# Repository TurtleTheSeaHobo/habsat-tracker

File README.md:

# HABSAT Tracker
*(awful acronym pending)*

This repository provides schematics and layouts for the hardware of a high-
altitude balloon tracker and sensor carrier of presently indeterminate name.

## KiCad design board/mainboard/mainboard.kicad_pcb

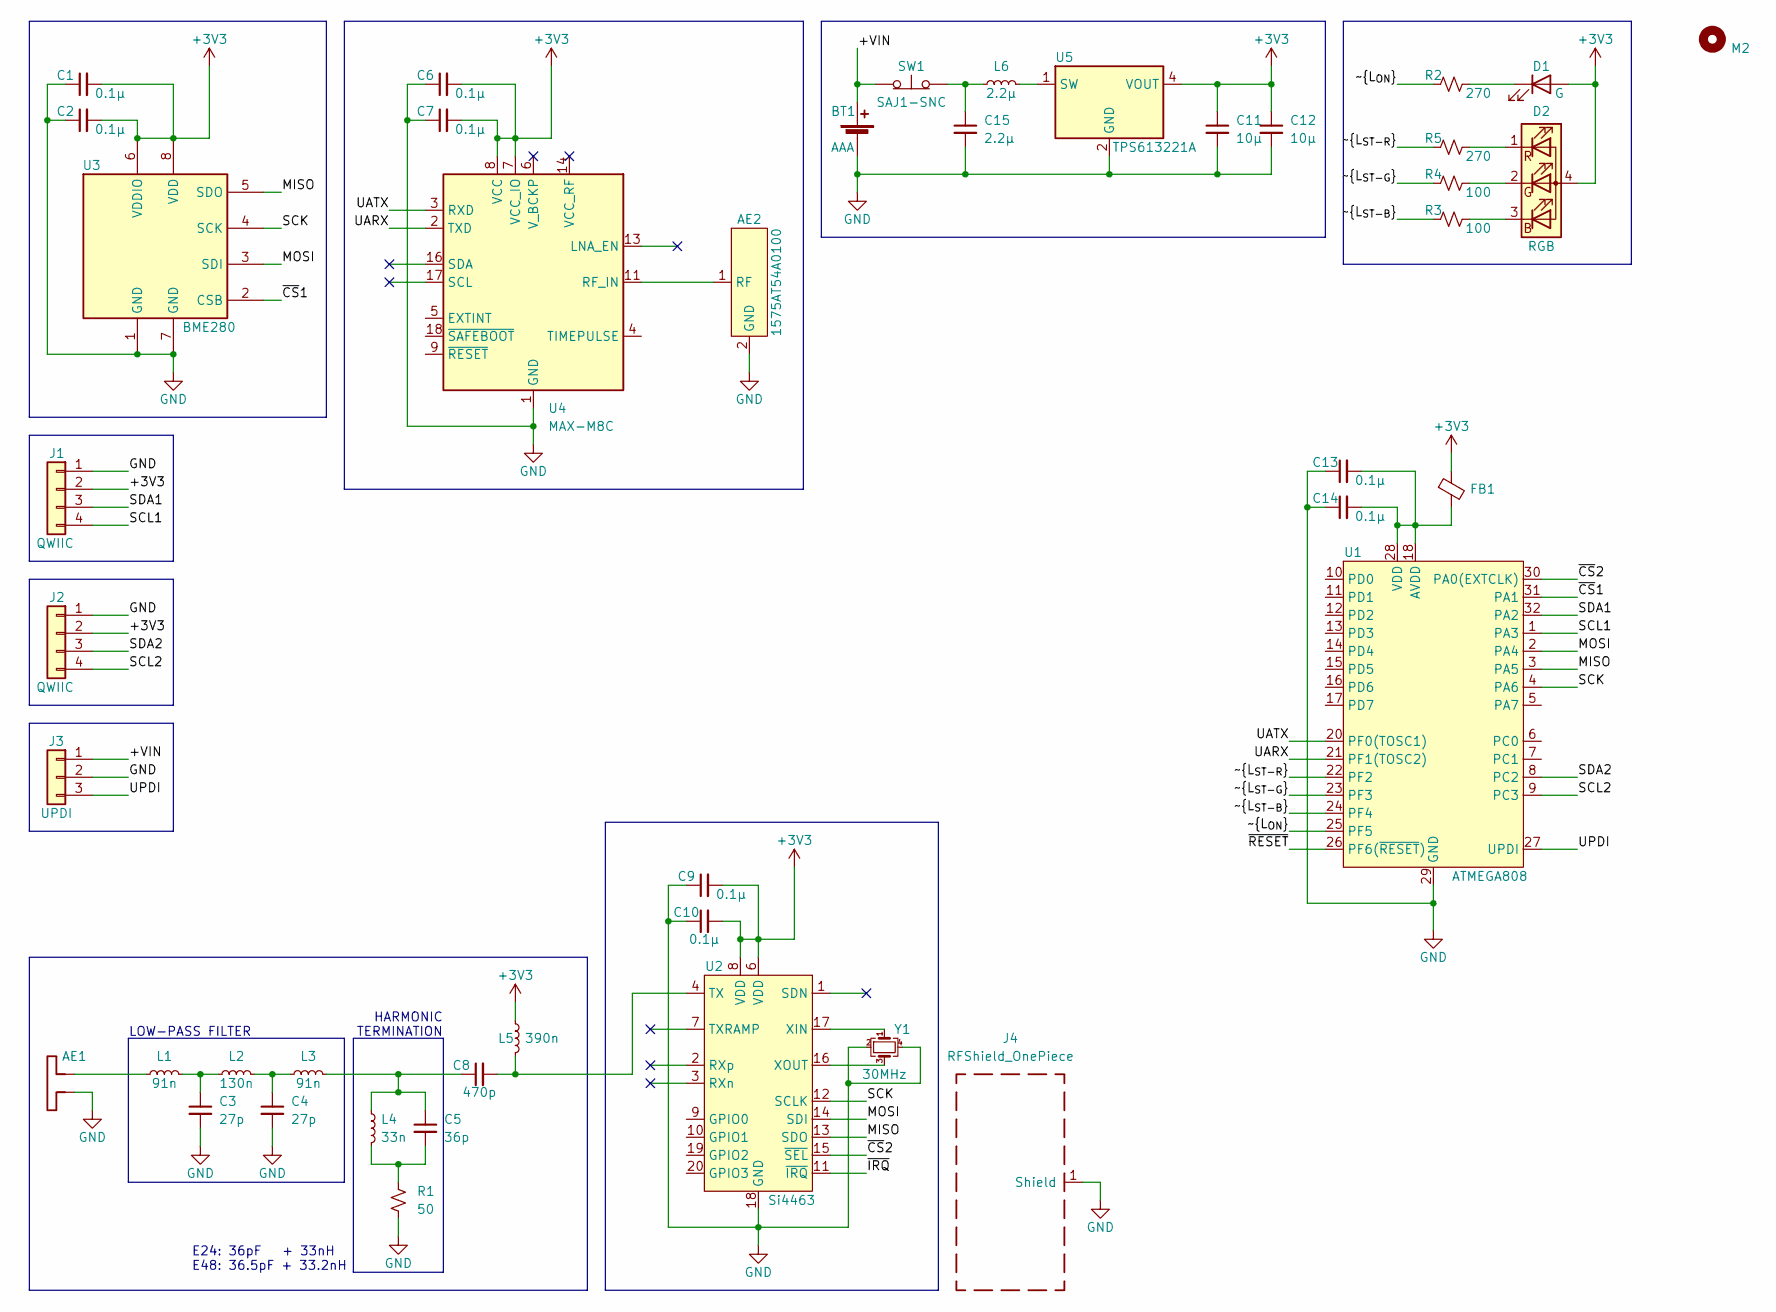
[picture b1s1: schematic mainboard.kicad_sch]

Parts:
AE1: Antenna_Dipole; AE_Pad
AE2: 1575AT54A0100; Johanson_AT54
BT1: AAA; BatteryHolder_Keystone_2466_1xAAA
C1, C2, C6, C7, C9, C10, C13, C14: 0.1µ; C_0402_1005Metric
C3, C4: 27p; C_0603_1608Metric
C5: 36p; C_0603_1608Metric
C8: 470p; C_0603_1608Metric
C11, C12: 10µ; C_0603_1608Metric
C15: 2.2µ; C_0603_1608Metric
D1: G; LED_0603_1608Metric
D2: RGB; LED_LiteOn_LTST-C19HE1WT
FB1: BEAD; L_0805_2012Metric
H1: M2; MountingHole_2.2mm_M2
J1, J2: QWIIC; JST_SH_SM04B-SRSS-TB_1x04-1MP_P1.00mm_Horizontal
J3: UPDI; PinHeader_1x03_P2.54mm_Vertical
J4: RFShield_OnePiece; Wuerth_36103205_20x20mm
L1, L3: 91n; L_0603_1608Metric
L2: 130n; L_0603_1608Metric
L4: 33n; L_0603_1608Metric
L5: 390n; L_0603_1608Metric
L6: 2.2µ; L_0805_2012Metric_Pad1.15x1.40mm_HandSolder
R1: 50; R_0603_1608Metric
R2, R5: 270; R_0402_1005Metric
R3, R4: 100; R_0402_1005Metric
SW1: SAJ1-SNC; SAJ1______N88SNCPT_
U1: ATMEGA808; TQFP-32_7x7mm_P0.8mm
U2: Si4463; QFN-20-1EP_4x4mm_P0.5mm_EP2.6x2.6mm_ThermalVias
U3: BME280; Bosch_LGA-8_2.5x2.5mm_P0.65mm_ClockwisePinNumbering
U4: MAX-M8C; ublox_MAX
U5: TPS613221A; SOT-23-5
Y1: 30MHz; Crystal_SMD_3225-4Pin_3.2x2.5mm

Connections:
+3V3: C1.2, C2.2, C6.2, C7.2, C9.2, C10.2, C11.1, C12.1, D1.2 (A), D2.4 (A), FB1.1, J1.2, J2.2, L5.1, U2.6 (VDD), U2.8 (VDD), U3.6 (VDDIO), U3.8 (VDD), U4.7 (VCC_IO), U4.8 (VCC), U5.4 (VOUT)
/+VIN: BT1.1 (+), J3.1, SW1.2 (B)
/MISO: U1.3 (PA5), U2.13 (SDO), U3.5 (SDO)
/MOSI: U1.2 (PA4), U2.14 (SDI), U3.3 (SDI)
/SCK: U1.4 (PA6), U2.12 (SCLK), U3.4 (SCK)
/SCL1: J1.4, U1.1 (PA3)
/SCL2: J2.4, U1.9 (PC3)
/SDA1: J1.3, U1.32 (PA2)
/SDA2: J2.3, U1.8 (PC2)
/UARX: U1.21 (PF1(TOSC2)), U4.2 (TXD)
/UATX: U1.20 (PF0(TOSC1)), U4.3 (RXD)
/UPDI: J3.3, U1.27 (UPDI)
/~CS1: U1.31 (PA1), U3.2 (CSB)
/~CS2: U1.30 (PA0(EXTCLK)), U2.15 (~SEL)
/~IRQ: U2.11 (~IRQ)
/~L_{ON}: R2.1, U1.25 (PF5)
/~L_{ST-B}: R3.1, U1.24 (PF4)
/~L_{ST-G}: R4.1, U1.23 (PF3)
/~L_{ST-R}: R5.1, U1.22 (PF2)
/~RESET: U1.26 (PF6(~RESET))
GND: AE1.1, AE2.2 (GND), AE2.4 (GND), BT1.2 (-), C1.1, C2.1, C3.2, C4.2, C6.1, C7.1, C9.1, C10.1, C11.2, C12.2, C13.1, C14.1, C15.2, J1.1, J2.1, J3.2, J4.1 (Shield), R1.2, U1.19 (GND), U1.29 (GND), U2.18 (GND), U2.21 (GND), U3.1 (GND), U3.7 (GND), U4.1 (GND), U4.10 (GND), U4.12 (GND), U5.2 (GND), Y1.2, Y1.4
unnamed: AE1.2, L1.1
unnamed: AE2.1 (RF), U4.11 (RF_IN)
unnamed: C3.1, L1.2, L2.1
unnamed: C4.1, L2.2, L3.1
unnamed: C5.1, C8.1, L3.2, L4.1
unnamed: C5.2, L4.2, R1.1
unnamed: C8.2, L5.2, U2.4 (TX)
unnamed: C13.2, C14.2, FB1.2, U1.18 (AVDD), U1.28 (VDD)
unnamed: C15.1, L6.1, SW1.1 (A)
unnamed: D1.1 (K), R2.2
unnamed: D2.1 (RK), R5.2
unnamed: D2.2 (GK), R4.2
unnamed: D2.3 (BK), R3.2
unnamed: L6.2, U5.1 (SW)
unnamed: U2.16 (XOUT), Y1.3
unnamed: U2.17 (XIN), Y1.1

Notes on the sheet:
E24: 36pF + 33nH E48: 36.5pF + 33.2nH
HARMONIC TERMINATION
LOW-PASS FILTER

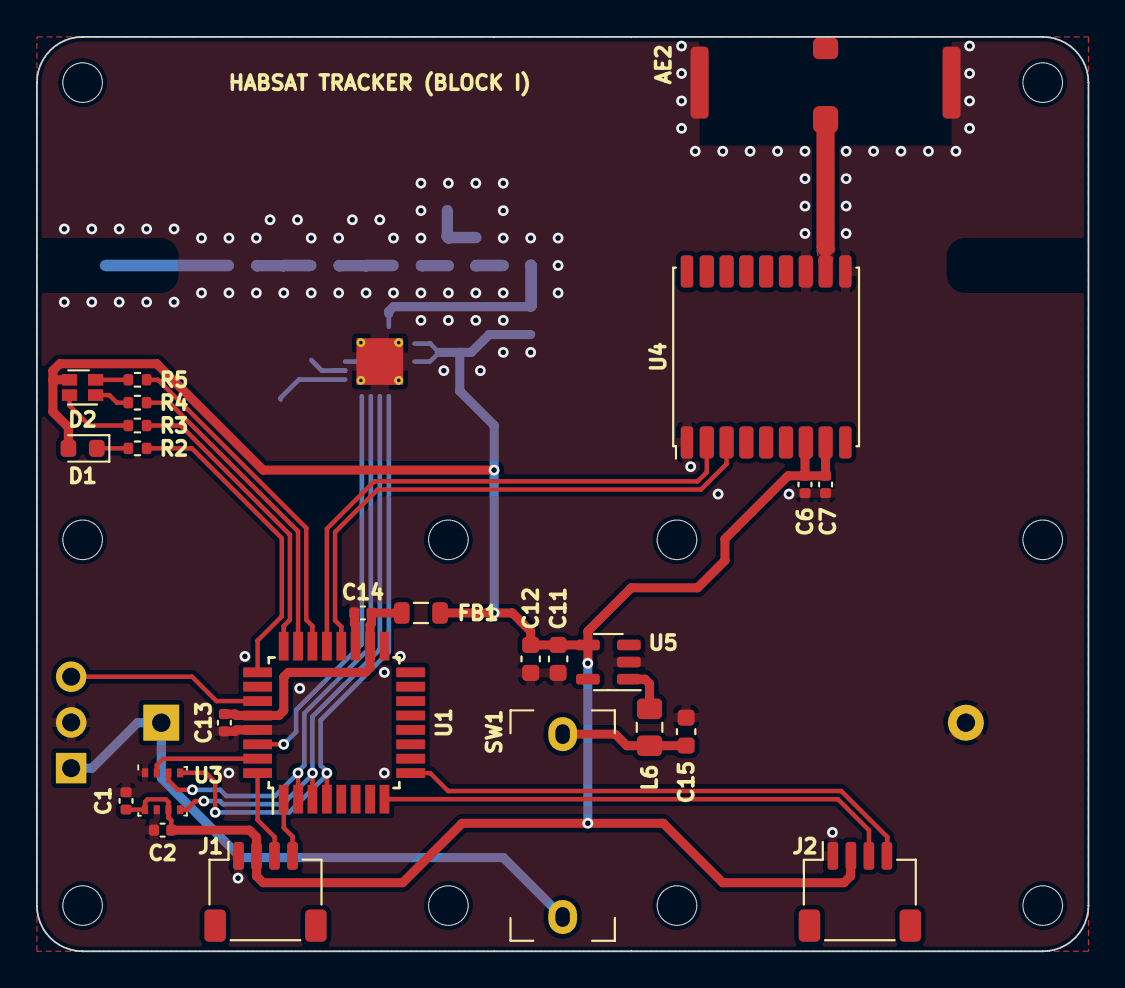
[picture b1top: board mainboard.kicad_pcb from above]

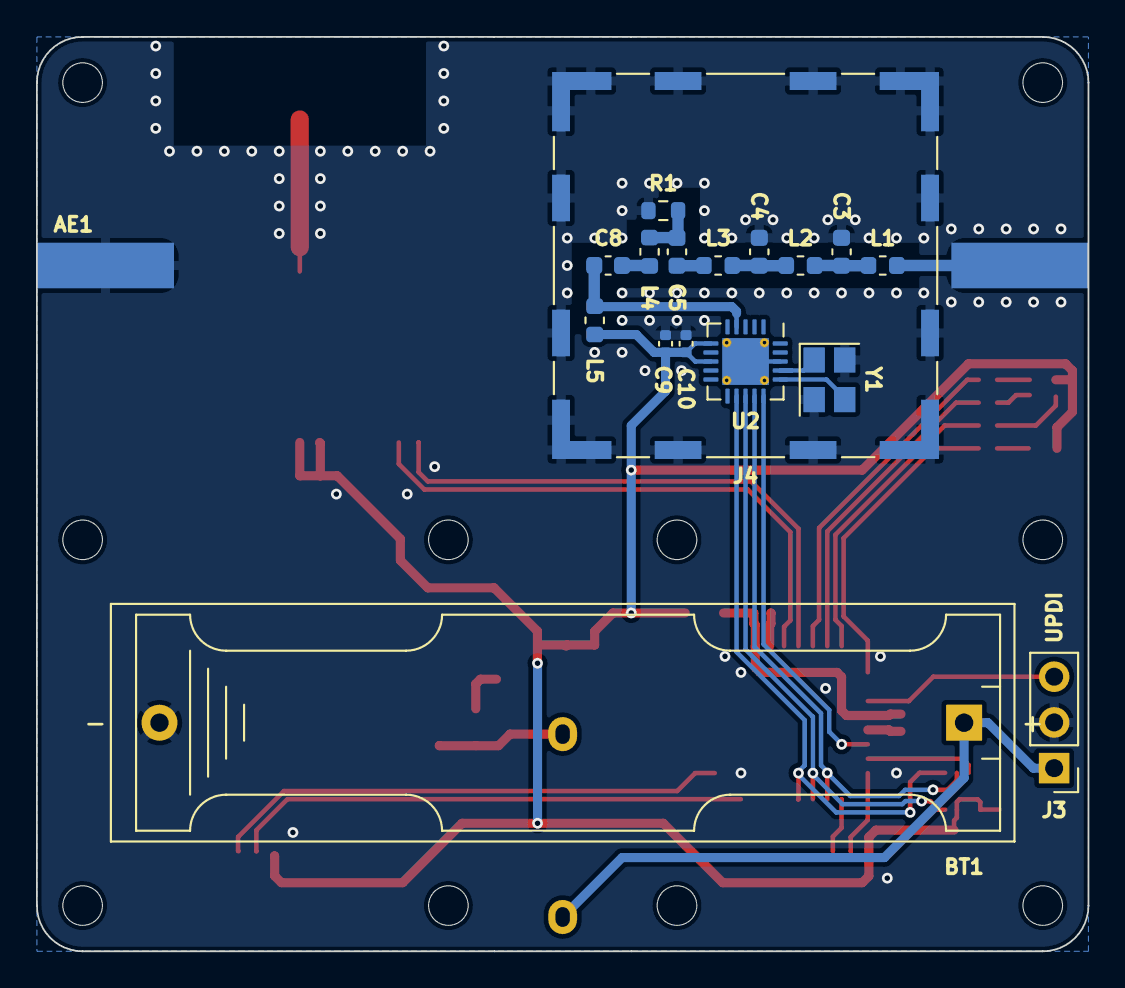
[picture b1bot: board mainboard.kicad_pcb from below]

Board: 2 copper layers, 58.4 x 50.8 mm, 53 parts (18 on the bottom side), 35 nets.

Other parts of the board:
H1#2, H1#3, H1#4, H1#5, H1#6, H1#7, H1#8, H1#9, H1#10: M2; MountingHole_2.2mm_M2

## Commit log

2023-04-16 added basic README
2023-04-16 added .gitignore
2023-04-16 added empty board so it won't cause weird commits later
2023-04-16 ignoring `fp-info-cache`
2023-04-18 `.gitignore` ignores backups/etc. recursively
2023-04-18 added basic uv sensor design
2023-04-20 ignore symbol backup files
2023-04-20 added ATmega808 symbol
2023-04-23 added early mainboard design
2023-05-01 added power supply and indicators
2023-05-05 ignore auto-save files
2023-05-05 added tx filter circuit values
2023-05-05 added designation and footprint to (most) components
2023-05-12 added GNSS antenna symbol/footprint
2023-05-12 ignore even more types of backup files
2023-05-12 added footprint for big dipole attachment
2023-05-12 added footprint for RBF switch
2023-05-12 latest PCB design update (will commit better henceforth)
2023-05-12 export mainboard VRML
2023-05-12 export mainboard VRM (forgot to add the actual file .-.)
2023-05-15 completed layouting for mainboard
2023-05-15 exported new mainboard VRML
2023-05-15 fixed silkscreen overlap at J1 designator
